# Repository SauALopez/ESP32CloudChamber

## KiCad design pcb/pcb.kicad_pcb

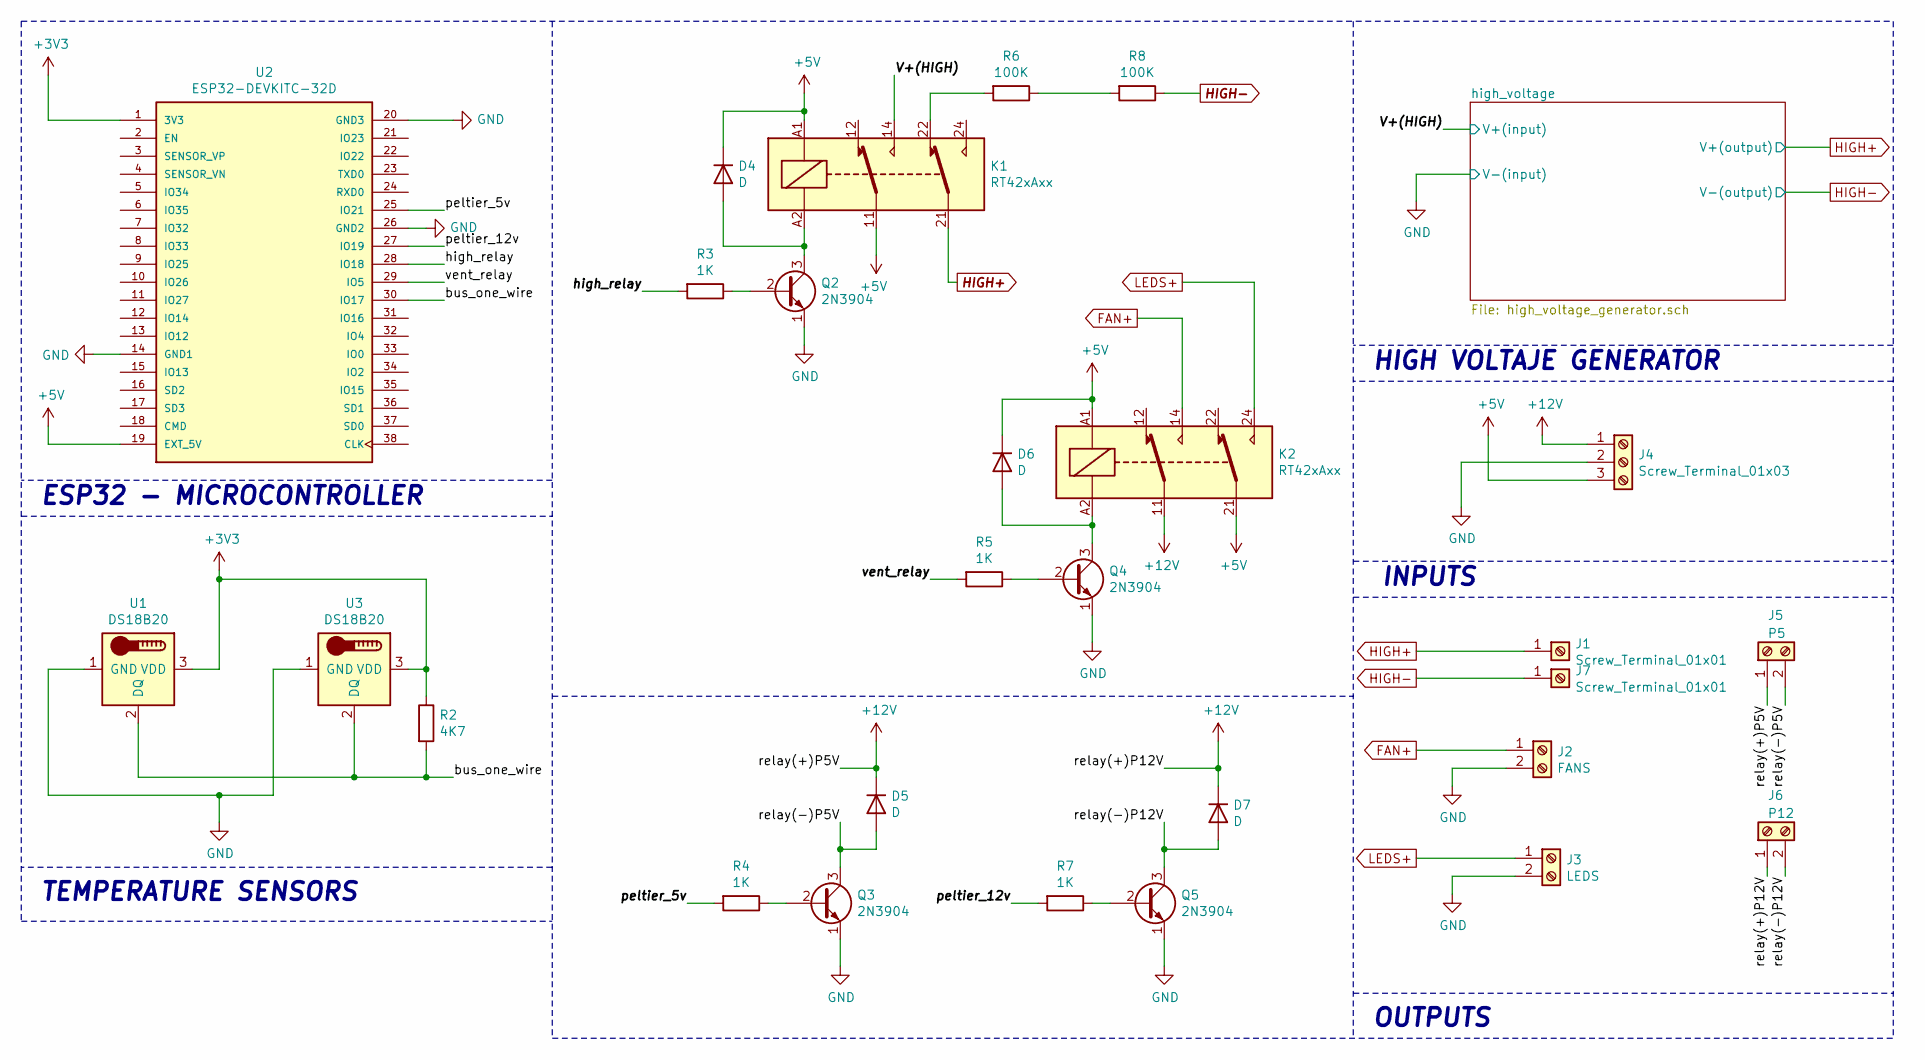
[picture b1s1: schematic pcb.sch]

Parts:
D4, D5, D6, D7: D; D_DO-15_P10.16mm_Horizontal
J1, J7: Screw_Terminal_01x01; TestPoint_Plated_Hole_D3.0mm
J2: FANS; TerminalBlock_bornier-2_P5.08mm
J3: LEDS; TerminalBlock_bornier-2_P5.08mm
J4: Screw_Terminal_01x03; TerminalBlock_bornier-3_P5.08mm
J5: P5; TerminalBlock_bornier-2_P5.08mm
J6: P12; TerminalBlock_bornier-2_P5.08mm
K1, K2: RT42xAxx; Relay_DPDT_Finder_30.22
Q2, Q3, Q4, Q5: 2N3904; TO-92_Inline
R2: 4K7; R_Axial_DIN0207_L6.3mm_D2.5mm_P10.16mm_Horizontal
R3, R4, R5, R7: 1K; R_Axial_DIN0207_L6.3mm_D2.5mm_P10.16mm_Horizontal
R6, R8: 100K; R_Axial_DIN0207_L6.3mm_D2.5mm_P10.16mm_Horizontal
U1, U3: DS18B20; TO-92_Inline
U2: ESP32-DEVKITC-32D; MODULE_ESP32-DEVKITC-32D; PARTREV 4

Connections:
+3V3: R2.1, U1.3 (VDD), U2.1 (3V3), U3.3 (VDD)
+5V: D4.1 (K), D6.1 (K), J4.3, K1.11, K1.A1, K2.21, K2.A1, U2.19 (EXT_5V)
+12V: D5.1 (K), D7.1 (K), J4.1, J5.1, J6.1, K2.11
/V+(HIGH): K1.14; also elsewhere on the board
/bus_one_wire: R2.2, U1.2 (DQ), U2.30 (IO17), U3.2 (DQ)
/high_relay: R3.2, U2.28 (IO18)
/peltier_5v: R4.2, U2.25 (IO21)
/peltier_12v: R7.2, U2.27 (IO19)
/relay(-)P5V: D5.2 (A), J5.2, Q3.3 (C)
/relay(-)P12V: D7.2 (A), J6.2, Q5.3 (C)
/vent_relay: R5.2, U2.29 (IO5)
FAN+: J2.1, K2.14
GND: J2.2, J3.2, J4.2, Q2.1 (E), Q3.1 (E), Q4.1 (E), Q5.1 (E), U1.1 (GND), U2.14 (GND1), U2.20 (GND3), U2.26 (GND2), U3.1 (GND); also elsewhere on the board
HIGH+: J1.1, K1.21; also elsewhere on the board
HIGH-: J7.1, R8.1; also elsewhere on the board
LEDS+: J3.1, K2.24
unnamed: D4.2 (A), K1.A2, Q2.3 (C)
unnamed: D6.2 (A), K2.A2, Q4.3 (C)
unnamed: K1.22, R6.2
unnamed: Q2.2 (B), R3.1
unnamed: Q3.2 (B), R4.1
unnamed: Q4.2 (B), R5.1
unnamed: Q5.2 (B), R7.1
unnamed: R6.1, R8.2

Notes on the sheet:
HIGH VOLTAJE GENERATOR
TEMPERATURE SENSORS
ESP32 - MICROCONTROLLER
INPUTS
OUTPUTS

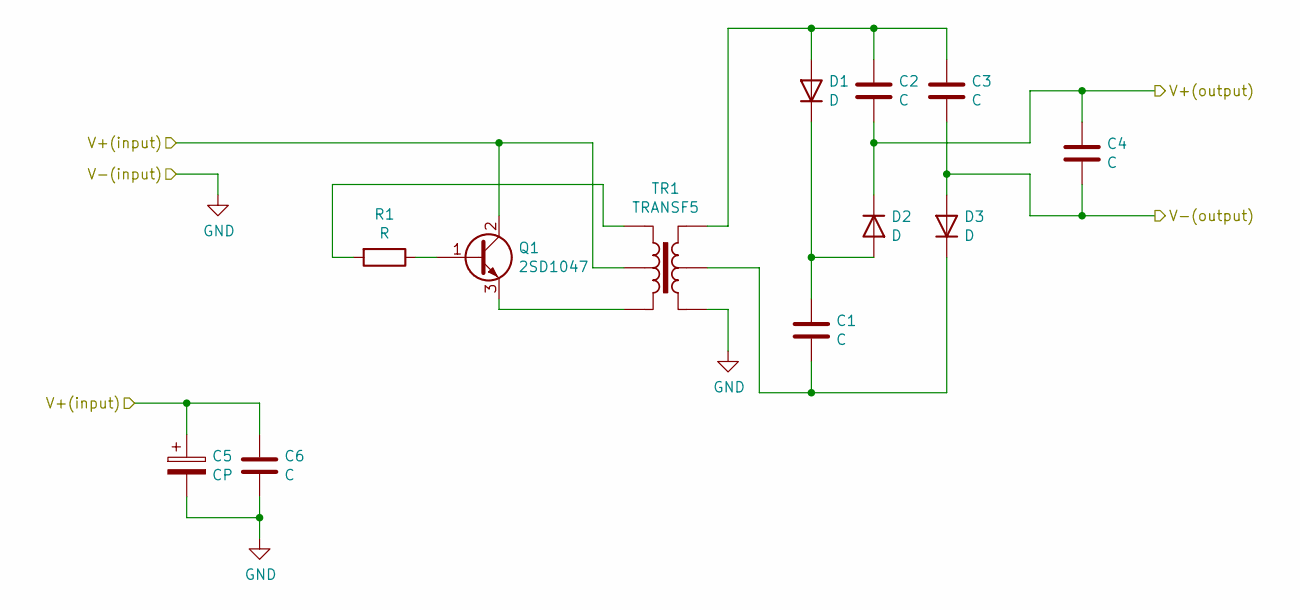
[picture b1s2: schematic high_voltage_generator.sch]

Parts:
C1, C2, C3, C6: C; C_Disc_D9.0mm_W2.5mm_P5.00mm
C4: C; C_Disc_D16.0mm_W5.0mm_P10.00mm
C5: CP; CP_Radial_D10.0mm_P2.50mm
D1, D2, D3: D; D_DO-15_P10.16mm_Horizontal
Q1: 2SD1047; TO-126-3_Vertical
R1: R; R_Axial_DIN0207_L6.3mm_D2.5mm_P10.16mm_Horizontal
TR1: TRANSF5; TRANSF6

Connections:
/V+(HIGH): C5.1, C6.1, Q1.2 (C), TR1.2; also elsewhere on the board
GND: C5.2, C6.2, TR1.4; also elsewhere on the board
HIGH+: C2.2, C4.1, D2.1 (K); also elsewhere on the board
HIGH-: C3.2, C4.2, D3.2 (A); also elsewhere on the board
unnamed: C1.1, D1.1 (K), D2.2 (A)
unnamed: C1.2, D3.1 (K), TR1.5
unnamed: C2.1, C3.1, D1.2 (A), TR1.6
unnamed: Q1.1 (B), R1.1
unnamed: Q1.3 (E), TR1.3
unnamed: R1.2, TR1.1

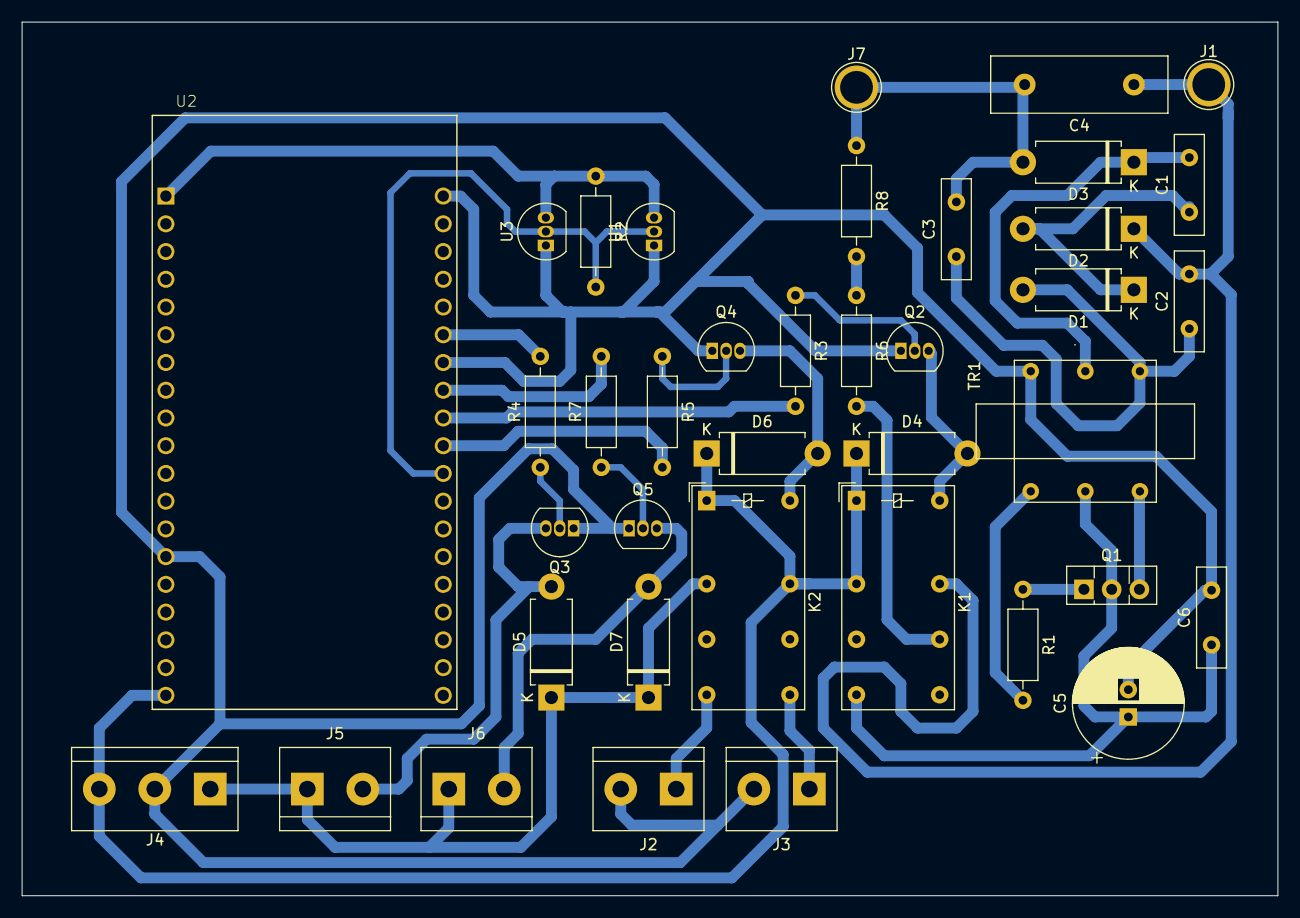
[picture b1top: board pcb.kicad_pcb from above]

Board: 2 copper layers, 115.0 x 80.0 mm, 39 parts (0 on the bottom side), 30 nets.

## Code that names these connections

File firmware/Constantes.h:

/**************
DEFINICIONES DE LOS PINES UTILIZADOS EN EL NODE MCU-32S
****************/

#define HIGH_RELAY 18
#define VENT_RELAY 5
#define PELTIER_5V 21
#define PELTIER_12V 19
#define BUS_ONE_WIRE 17



/**************
CONSTANTES DE LA CONFIGURACION DEL WIFI - EL SERVIDOR MQTT
****************/

const char* ssid = "SSID_NAME";
const char* password = "SSID_PWD";

//const char* mqtt_server = "test.mosquitto.org";
const char* mqtt_server = "SERVER_NAME_OR_IP";   //MQTT DEVELOPMENT IP
const int mqtt_port = 8883;
const char* mqtt_user = "USERNAME";
const char* mqtt_pwd = "PASSWORD";
const char* mqtt_key_client = "EcFmUsAcCL"; //MQTT ALIVE-CLIENT KEY VERIFICATION
const char* mqtt_key_web = "EcFmUsAcW";    //MQTT ALIVE-WEB KEY VERIFICATION
const char* syncrostatus = "sync";



//TOPICS TO PUBLISH
#define TOPIC_COMMANDS_WEB "commandsweb"
#define TOPIC_VALUE1 "value1"
#define TOPIC_VALUE2 "value2" 
#define TOPIC_STATUS "status"
//TOPIC TO SUBSCRIBE
#define TOPIC_COMMANDS "commands"


//GLOBAL OBJECTS
WiFiClientSecure espClient;
PubSubClient client(espClient);
OneWire oneWire(BUS_ONE_WIRE);
DallasTemperature sensors(&oneWire);
// GLOBAL VARIABLES
bool general = false;
bool alive_send = false;
bool isalive = false;
long time_web_alive = 0;
long last = 0;
int number_devices =0;

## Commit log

2021-04-06 BasicWebControl & Firmware
2021-04-06 Gitignore
2021-05-14 3D desing of cloudchamber
2021-05-14 Statci webcontrol alternative
2021-05-14 Firmware for ESP32 microcontroller
2021-05-14 PCB design
